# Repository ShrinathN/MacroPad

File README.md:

# MacroPad
A simple Pi Pico based macropad.
Can be assembled with mechanical keyswitches (3 pin and single pin). Can optionally include nRF24L01+ RF module.

# Fully assembled

# PCB

# Enclosure

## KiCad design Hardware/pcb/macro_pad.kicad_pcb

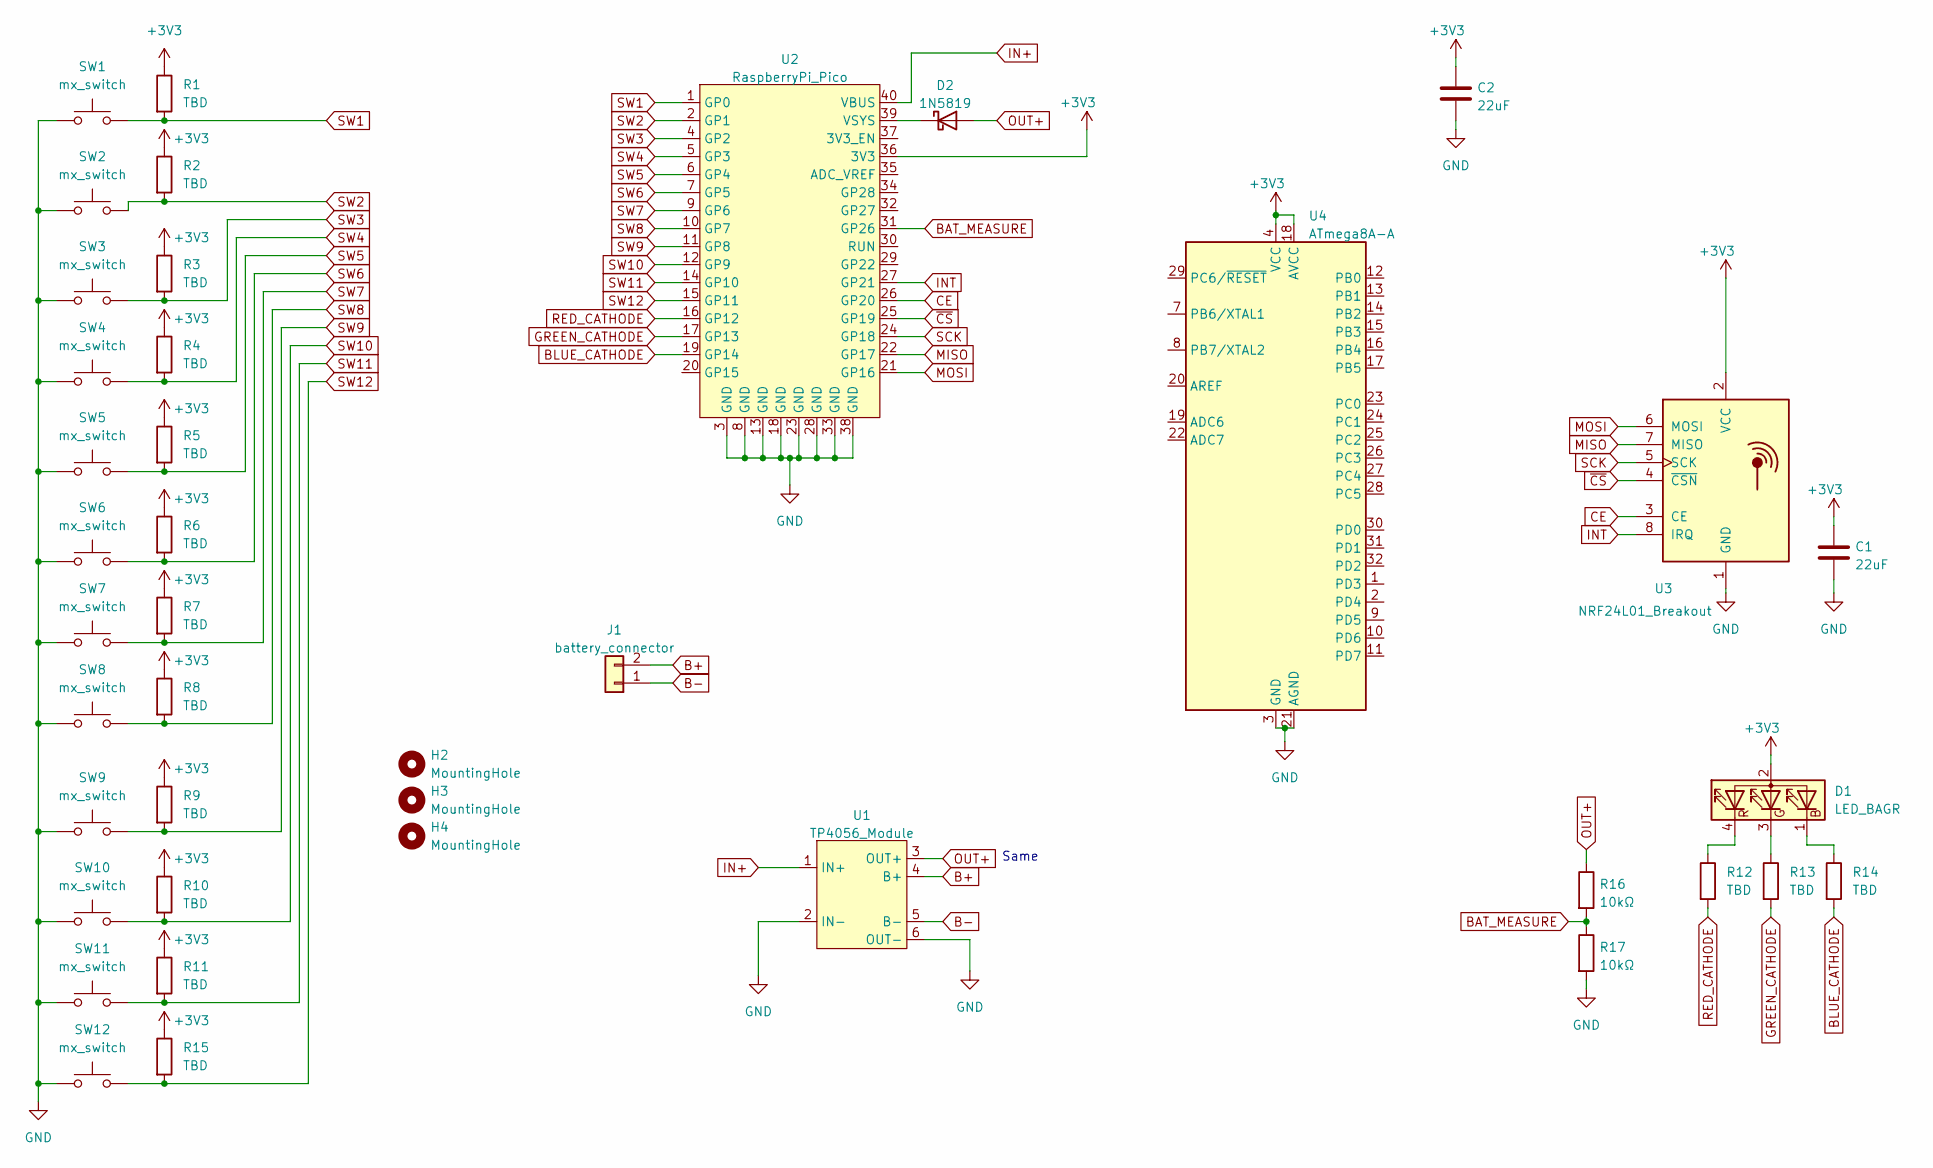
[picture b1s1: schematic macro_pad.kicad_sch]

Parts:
C1, C2: 22uF; C_0805_2012Metric
D1: LED_BAGR; PinHeader_1x04_P1.27mm_Vertical
D2: 1N5819; D_DO-41_SOD81_P10.16mm_Horizontal
H2, H3, H4: MountingHole; MountingHole_5mm
J1: battery_connector; PinHeader_1x02_P2.54mm_Vertical
R1, R2, R3, R4, R5, R6, R7, R8, R9, R10, R11, R12, R13, R14, R15: TBD; R_1206_3216Metric
R16, R17: 10kΩ; R_1206_3216Metric
SW1, SW2, SW3, SW4, SW5, SW6, SW7, SW8, SW9, SW10, SW11, SW12: mx_switch; SW_Cherry_MX_1.00u_PCB
U1: TP4056_Module; tp4056_module
U2: RaspberryPi_Pico; raspberry_pi_pico
U3: NRF24L01_Breakout; nRF24L01_Breakout
U4: ATmega8A-A; TQFP-32_7x7mm_P0.8mm

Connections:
+3V3: C1.1, C2.1, D1.2 (A), R1.1, R2.1, R3.1, R4.1, R5.1, R6.1, R7.1, R8.1, R9.1, R10.1, R11.1, R15.1, U2.36 (3V3), U3.2 (VCC), U4.4 (VCC), U4.6 (VCC), U4.18 (AVCC)
B+: J1.2, U1.4 (B+)
B-: J1.1, U1.5 (B-)
BAT_MEASURE: R16.2, R17.1, U2.31 (GP26)
BLUE_CATHODE: R14.2, U2.19 (GP14)
CE: U2.26 (GP20), U3.3 (CE)
GND: C1.2, C2.2, R17.2, SW1.1, SW2.1, SW3.1, SW4.1, SW5.1, SW6.1, SW7.1, SW8.1, SW9.1, SW10.1, SW11.1, SW12.1, U1.2 (IN-), U1.6 (OUT-), U2.3 (GND), U2.8 (GND), U2.13 (GND), U2.18 (GND), U2.23 (GND), U2.28 (GND), U2.33 (GND), U2.38 (GND), U3.1 (GND), U4.3 (GND), U4.5 (GND), U4.21 (AGND)
GREEN_CATHODE: R13.2, U2.17 (GP13)
IN+: U1.1 (IN+), U2.40 (VBUS)
INT: U2.27 (GP21), U3.8 (IRQ)
MISO: U2.22 (GP17), U3.7 (MISO)
MOSI: U2.21 (GP16), U3.6 (MOSI)
unnamed: D2.1 (K), U2.39 (VSYS)
unnamed: D1.4 (RK), R12.1
unnamed: D1.3 (GK), R13.1
unnamed: D1.1 (BK), R14.1
OUT+: D2.2 (A), R16.1, U1.3 (OUT+)
RED_CATHODE: R12.2, U2.16 (GP12)
SCK: U2.24 (GP18), U3.5 (SCK)
SW1: R1.2, SW1.2, U2.1 (GP0)
SW2: R2.2, SW2.2, U2.2 (GP1)
SW3: R3.2, SW3.2, U2.4 (GP2)
SW4: R4.2, SW4.2, U2.5 (GP3)
SW5: R5.2, SW5.2, U2.6 (GP4)
SW6: R6.2, SW6.2, U2.7 (GP5)
SW7: R7.2, SW7.2, U2.9 (GP6)
SW8: R8.2, SW8.2, U2.10 (GP7)
SW9: R9.2, SW9.2, U2.11 (GP8)
SW10: R10.2, SW10.2, U2.12 (GP9)
SW11: R11.2, SW11.2, U2.14 (GP10)
SW12: R15.2, SW12.2, U2.15 (GP11)
~CS: U2.25 (GP19), U3.4 (~CSN)

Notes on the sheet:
Same

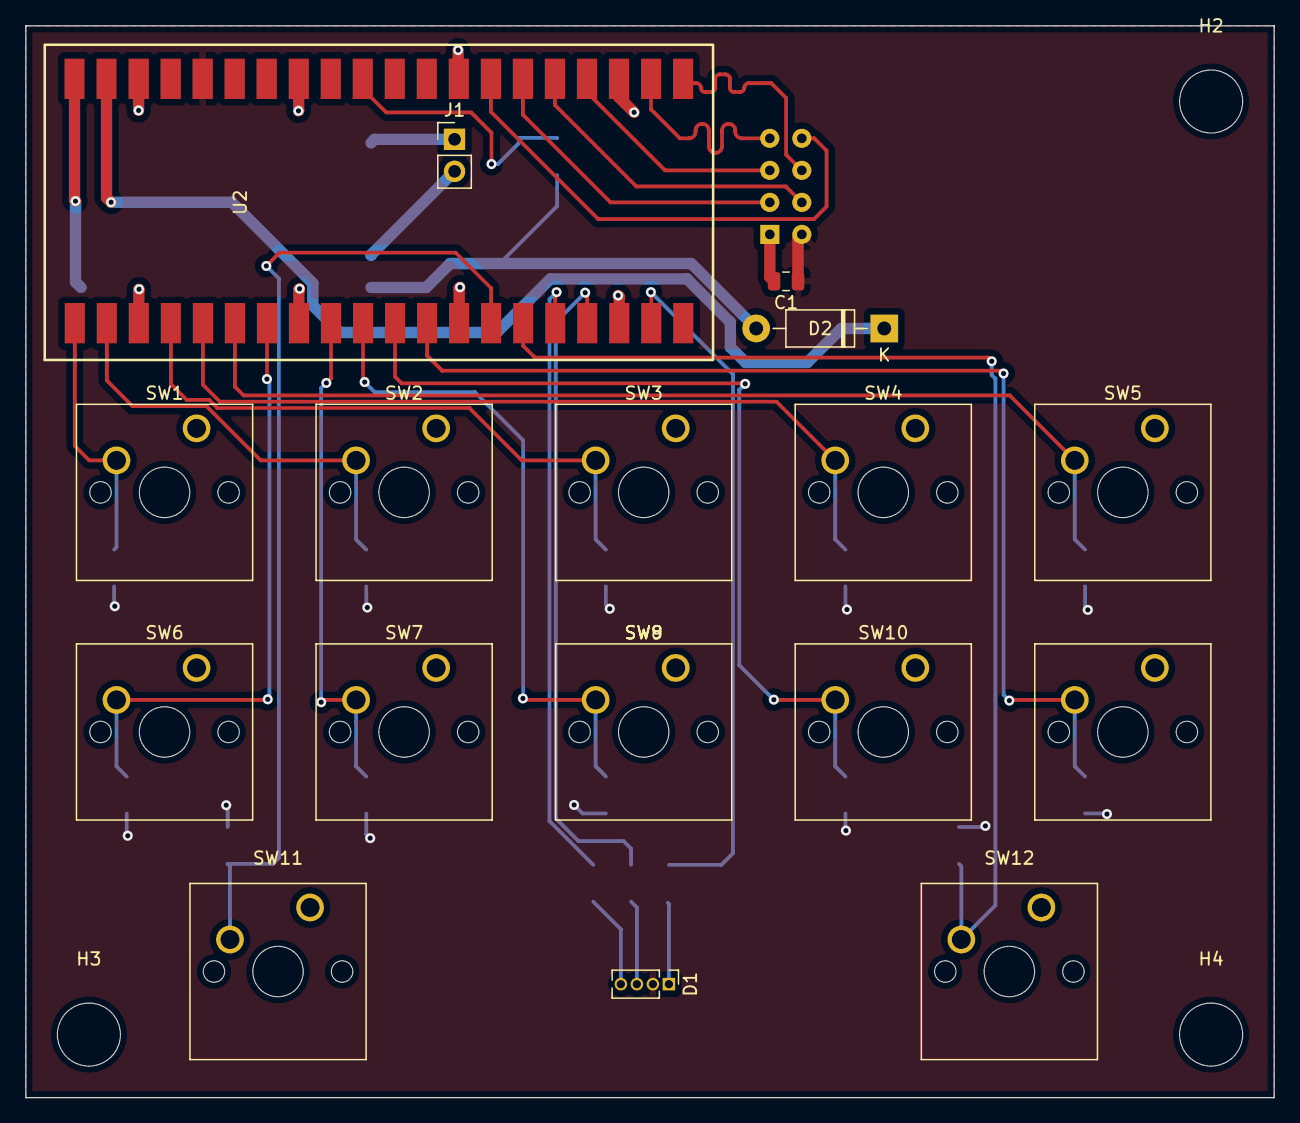
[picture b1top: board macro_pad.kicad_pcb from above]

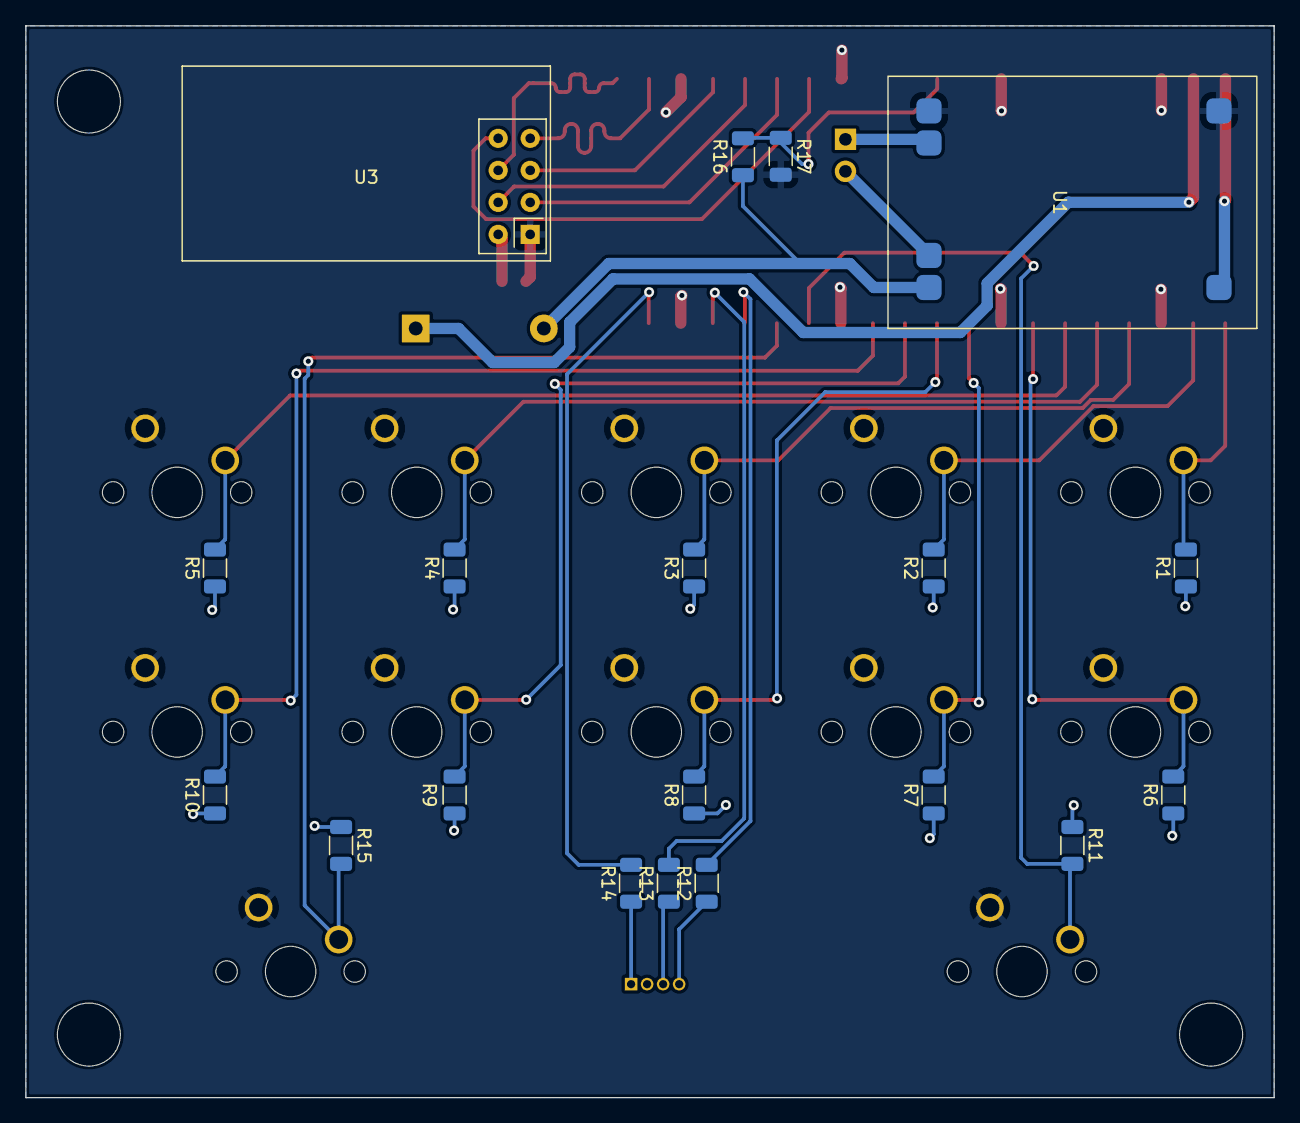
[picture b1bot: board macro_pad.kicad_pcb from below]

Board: 2 copper layers, 99.0 x 85.0 mm, 39 parts (19 on the bottom side), 32 nets.

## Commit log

2022-07-30 Added all the files
2022-07-30 Added board pictures
2024-06-08 Basic FW
